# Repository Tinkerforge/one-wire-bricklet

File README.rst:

One Wire Bricklet
=================

This repository contains the firmware source code and the hardware design
files. The documentation generator configs can be found at
https://github.com/Tinkerforge/generators

Repository Content
------------------

software/:
 * examples/: Examples for all supported languages
 * build/: Compiled files
 * src/: Source code of firmware
 * Makefile: Makefile to build project

hardware/:
 * Contains KiCad project files and additionally schematics as PDF

datasheets/:
 * Contains datasheets for sensors and complex ICs that are used

Hardware
--------

The hardware is designed with the open source EDA Suite KiCad
(http://www.kicad.org). Before you are able to open the files,
you have to install the Tinkerforge kicad-libraries
(https://github.com/Tinkerforge/kicad-libraries). You can either clone
them directly in hardware/ or clone them in a separate folder and
symlink them into hardware/
(ln -s kicad_path/kicad-libraries project_path/hardware). After that you
can open the .pro file in hardware/ with KiCad and from there view and
modify the schematics and the PCB layout.

Software
--------

If you want to do your own Brick/Bricklet firmware development we highly
recommend that you use our build environment setup script and read the
tutorial (https://www.tinkerforge.com/en/doc/Tutorials/Tutorial_Build_Environment/Tutorial.html).

To compile the C code we recommend you to install the newest GNU Arm Embedded
Toolchain (https://launchpad.net/gcc-arm-embedded/+download).
You also need to install bricklib2 (https://github.com/Tinkerforge/bricklib2).

You can either clone it directly in software/src/ or clone it in a
separate folder and symlink it into software/src/
(ln -s bricklib_path/bricklib2 project_path/software/src/). Finally make sure to
have CMake installed (http://www.cmake.org/cmake/resources/software.html).

After that you can build the firmware by invoking make in software/.
The firmware (.zbin) can then be found in software/build/ and uploaded
with brickv (click button "Flashing" on start screen).

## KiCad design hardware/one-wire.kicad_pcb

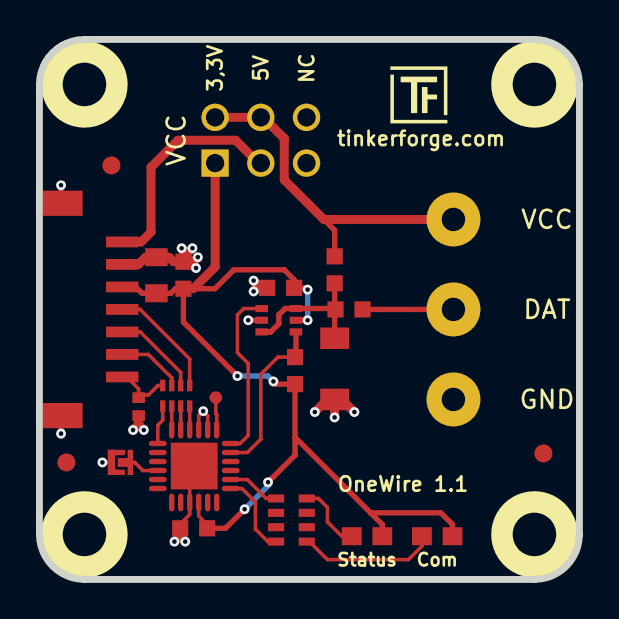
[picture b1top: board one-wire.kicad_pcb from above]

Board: 2 copper layers, 30.0 x 30.0 mm, 28 parts (1 on the bottom side), 22 nets.

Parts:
C1: 10uF; C0805
C2: 220pF; C0402F
C3: 1uF; C0603F
C4, C5: 100nF; C0603F
D1: blue; D0603E
D2: 5V; MiniMelf
D3: green; D0603E
Fiducial_Mark: VAL**; Fiducial_Mark
Fiducial_Mark#2, Fiducial_Mark#3: VAL**; Fiducial_Mark
P1: CON-SENSOR2
P2: DEBUG; DEBUG_PAD
P3: BOOT; SolderJumper
P4: CONN_02X03; pin_array_3x2
P5: CONN_01X03; AKL_5_3
R1: 100; R0603F
R2, R3: 4k7; R0603F
RP1: 82; 4X0402
RP2: 1k; 4X0603
U1: XMC1302; QFN24-4x4mm-0.5mm
U2: NC7WZ07; SC70-6
U3, U4, U5, U6: DRILL; DRILL_NP
VAL: CE_5mm

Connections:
3V3: C1.2, C3.2, C4.1, C5.2, D1.1, D3.1, P1.3, P4.1, R3.1, U1.10, U2.5
+5V: P1.1, P4.3
DAT: P5.2, R1.1
GND: C1.1, C2.1, C3.1, C4.2, C5.1, D2.1, P1.2, P1.EP, P3.1, P5.3, U1.9, U1.20, U1.21, U1.EXP, U2.2
unnamed: C2.2, P1.7, RP1.4
unnamed: D1.2, RP2.1
unnamed: D2.2, R1.2, R2.2, U2.3, U2.6
unnamed: D3.2, RP2.4
unnamed: P1.4, RP1.1
unnamed: P1.5, RP1.2
unnamed: P1.6, RP1.3
unnamed: P2.1, U1.19
unnamed: P3.2, U1.4
unnamed: RP2.5, U1.13
unnamed: RP2.8, U1.14
RX: R3.2, U1.17, U2.4
S-CLK: RP1.7, U1.23
S-CS: RP1.8, U1.22
S-MISO: RP1.5, U1.1
S-MOSI: RP1.6, U1.24
TX: U1.18, U2.1
VCC: P4.2, P4.4, P5.1, R2.1

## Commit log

2018-05-07 Add buffer datasheet
2018-05-07 Add schematic
2018-05-07 fix rx schematic
2018-05-07 Add another led
2018-05-07 Assign footprints
2018-05-07 Assign missing footprint
2018-05-07 Add layout (tbc)
2018-05-08 one wire bricklet fully routed
2018-05-11 Change 3d model color
2018-05-15 Add .gitignore
2018-05-17 add z diode hint
2018-05-18 Add stub firmware for One Wire Bricklet
2018-05-25 Add 1-wire API and implementation
2018-05-25 Add hint to App Note where code comes from
2018-05-25 Use correct constant
2018-05-25 Change MCU from XMC11 to XMC13, so we have more flash for future functions. We might want to add functions like "temperature_read_ds18b20" and it is currently unclear how many of those functions we w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
    With XMC11 we would have only ~2kb left, with XMC13 we have 18kb left!
2018-05-25 Change baudrate with precomputed values, the computation in the SetBaudrate function is way too slow
2018-06-06 set origin, specify zener
2018-06-18 Change capacitor footprint(s) to C0402F
2018-06-28 Fix readme
2018-07-11 Add Makefile with docker support
2018-07-11 Update directory structure and build instructions
2018-07-11 Remove obsolete generate_makefile scripts
2018-07-17 respecify processor XMC1100 -> 1300
2018-07-17 Turn logging off
2018-07-30 change protection diode to minimelf
2018-07-31 Add 3d model (*.FCStd & *.step)
2018-09-10 Add incomplete examples
2018-09-10 Complete partially auto-generated Python example
2018-09-10 Complete partially auto-generated C example
2018-09-10 Complete partially auto-generated C# example
2018-09-10 Complete partially auto-generated Delphi example
2018-09-10 Complete partially auto-generated Java example
2018-09-10 Remove outdated fixme
2018-09-11 Complete partially auto-generated JavaScript example
2018-09-11 Complete partially auto-generated Matlab example
2018-09-11 Complete partially auto-generated Perl example
2018-09-11 Complete partially auto-generated PHP example
2018-09-11 Complete partially auto-generated Ruby example
2018-09-11 Complete partially auto-generated Shell example
2018-09-11 Complete partially auto-generated VB.NET example
2018-09-11 Complete partially auto-generated Mathematica example
    This is currently untested
2018-09-27 examples: Fix compile errors and unify style
2018-10-02 Add BOOTLOADER_FIX_POINTER_END define
2018-10-04 Add rev to changelog
2018-10-10 fix one wire routing
2018-10-10 add errata file
2018-10-12 increase hardware version to 1.1
    * previous fixed (rx,tx moved) will be used
    * add version detection pins (gnd)
    * increase version number
2018-10-16 Remove in-development marker
2018-11-06 Add rust examples
2018-11-07 rust: Accept host names for ip connection, fix naming inconsistencies
2018-12-14 Add go examples.
2018-12-18 go: Change import path.
2018-12-18 go: Change import path again.
2018-12-19 Fix two's complement handling in DS18B20 example.
2018-12-19 js: Fix two's complement handling in DS18B20 example.
2018-12-19 js: Fix import path in example.
2018-12-20 rust: Reformat examples.
2019-01-24 mqtt: Add examples.
2019-01-24 mqtt: Remove executable bit in example permissions.
2019-01-24 go: Minor example fixes.
2019-01-24 mqtt: Minor example fixes.
2019-01-29 Clean up style and fix some minor problems in examples
2019-05-29 Increase version for new release (changes in bricklib2)
2020-01-14 examples: Use python3 input by default.
2020-02-05 Use Integer instead of Byte for shifting to work
2020-03-18 Whitespace
2020-03-18 vbnet: Fix typo
2020-03-18 rust: Update to new skeleton
2020-04-03 Add openHAB examples.
2020-04-07 delphi: Fix format string handling
2020-04-07 vbnet: Fix byte shift
2020-04-07 rust: Fix format string
2020-04-07 python: Fix wrong label
2020-04-07 matlab: Fix shift operator usage
2020-04-07 go: Fix format string
2020-04-07 examples: rust: Always block when calling bindings functions.
2020-04-07 examples: rust: Only block on second write_command.
2020-08-19 Add uc examples.
2020-08-25 uc: Adapt example to new skeleton
2020-08-27 uc: Fix warnings.
2020-08-31 uc: Use fixed-with placeholders in format strings.
2020-09-02 uc: Add example driver note.
2021-05-27 javascript: Remove incomplete marker
2021-10-25 Update KiCad link
    https://www.kicad.org/blog/2021/10/Avoid-links-to-former-kicad-domain/
2022-01-05 specify processor xmc1302
2022-04-19 examples: uc: Rename TF_HalContext to TF_HAL.
2022-04-26 uc: Adapt to bindings changes
2022-07-06 Add license files.
2023-04-12 Add support for hardware version 1.1
2023-04-12 Add revision for 2.0.2
2024-02-21 fix rust example: prevent overflow due to shifting a 8 bit value by 8 bits.
2025-10-04 Fix compatibility with new Docker build image (GCC 14.2.1)

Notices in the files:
hardware/one-wire.kicad_pcb:
Licensed under CERN OHL v.1.1
Copyright (©) 2018, L.Lauer
Copyright Tinkerforge GmbH 2018.
This documentation describes Open Hardware and is licensed under the
CERN OHL v. 1.1.
